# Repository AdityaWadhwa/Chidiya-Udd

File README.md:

# Chidiya-Udd
The title of the project “Chidiya udd” describes a popular Indian game which almost each Indian has played in their childhood. 

In the contemporary form, a person becomes a moderator and says the name of many objects which can either fly or they don’t and the players have to raise their finger in accordance with the object. 

This project replicates exactly the contemporary form but eliminating the need of a moderator which is fulfilled by the microcontroller. 
The project is developed under the guidance of Mr. D.V Gadre, CEDT lab in Netaji Subhas Institute of Technology (now, Netaji Subhas University of Technology). 

It was developed alongside my friend Sumiran Bhasin (https://github.com/sumiran14)

The microcontroller chosen is Texas Instruments low power device MSP430G2553.  

This project also interfaces two external SPI devices, the Graphics LCD and a flash memory; a speaker is used for the voice output.
The input from the player  is taken through a capacitive touch interface. 

As of now, it speaks only speaks in one language and only the name of the object. The next versions of the same project will have its own battery dependent power supply, better voice quality and more speed

The audio files are first downloaded (using Google translate) and converted and sampled at 8kHz and stored in 8 bit format(because human voice has maximum frequency of 4 kHZ and we sample it at at least twice that frequency) 
and saved in .wav format. Then using a software "WAVToCode" they are easily converted into c files. 
The data in the C files is really large so any microcontroller memory can’t fit all of that. 
So the data is sent through a python program from the PC to an Arduino and then written in external SPI Flash memory through Arduino.

When the data has to be played, MSP430 first fetches the data from SPI flash. 
That data decides the duty cycle of the PWM wave.The PWM wave is then sent as an input to a PAM IC and finally to a speaker to hear us the voice. As the data is sampled at 8Khz the duty cycle of the PWM wave has to be changed after every 1/8000th of a second i.e the next data is fetched from the external memory and played for 1/8000th of a second. 

The Graphics LCD is used to display the score. The code for the Graphics LCD is inspired by a blog by Rohit Gupta. 
Since timers are used for generating PWM, developing our own code for capacitive touch sensing was essential. 

In general, capacitive touch works on the basis of an oscillator with a capacitor. 
For a fixed period of time, the number of oscillations in that period would not vary much if the capacitance doesn’t change. 
Due to human interaction, capacitance of the circuit changes drastically and the variation in oscillations in the fixed time are different by a substantial amount causing us to detect a touch. 
MSP430G2553 have built in pin oscillators and by changing some values in registers we can make them enabled and use them as a clock source to one of the timers. 

The overall codeflow is that at the start the player has a fixed score of 9. The game doesn’t start as soon as the finger of the player isn’t on the touchplate and as one loses their score decreases. A random number generator generates a random number which calls a specific object. When the player has score 0 the reset button has to be pressed to play the game again.

Each code and EAGLE files for the same have been attached.

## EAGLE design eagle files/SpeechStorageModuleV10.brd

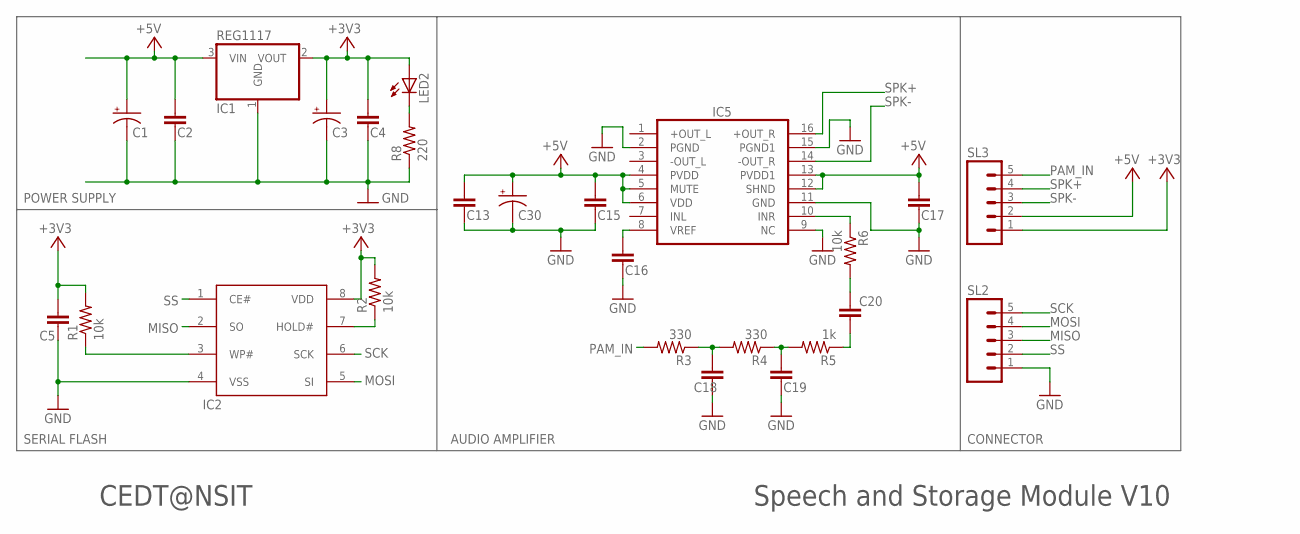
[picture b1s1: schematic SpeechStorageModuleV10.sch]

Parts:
C1, C3: 10u; C/6032-28R
C2, C4: 0.1uF; C1206
C5, C18: 0.1u; C0805
C13, C15, C17: 1uf; C1206
C16: 0.1uf; C1206
C19: 0.1uf; C0805
C20: 0.47uF; C0805
C30: 100u; C/6032-28R
IC1: REG1117; SOT223
IC2: SST25VF040B_SPI_FLASH; SOIC08
IC5: PAM8403; SOP-16
LED2: LED0805; CHIPLED_0805
R1, R2, R6: 10k; R0805
R3, R4: 330; R0805
R5: 1k; R0805
R8: 220; R0805
SL2, SL3: M05; 05P

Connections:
+3V3: C3.+, C4.2, C5.1, IC1.2 (VOUT), IC2.8 (VDD), LED2.A, R1.2, R2.2, SL3.1
+5V: C1.+, C2.2, C13.1, C15.2, C17.2, C30.+, IC1.3 (VIN), IC5.4 (PVDD), IC5.5 (MUTE), IC5.6 (VDD), IC5.12 (SHND), IC5.13 (PVDD1), SL3.2
GND: C1.-, C2.1, C3.-, C4.1, C5.2, C13.2, C15.1, C16.2, C17.1, C18.2, C19.2, C30.-, IC1.1 (GND), IC2.4 (VSS), IC5.2 (PGND), IC5.9 (NC), IC5.11 (GND), IC5.15 (PGND1), R8.1, SL2.1
MISO: IC2.2 (SO), SL2.3
MOSI: IC2.5 (SI), SL2.4
unnamed: IC2.7 (HOLD#), R2.1
unnamed: C18.1, R3.1, R4.2
unnamed: IC2.3 (WP#), R1.1
unnamed: C19.1, R4.1, R5.2
unnamed: C20.1, R5.1
unnamed: C20.2, R6.2
unnamed: LED2.C, R8.2
unnamed: IC5.10 (INR), R6.1
unnamed: C16.1, IC5.8 (VREF)
PAM_IN: R3.2, SL3.5
SCK: IC2.6 (SCK), SL2.5
SPK+: IC5.16 (+OUT_R), SL3.4
SPK-: IC5.14 (-OUT_R), SL3.3
SS: IC2.1 (CE#), SL2.2

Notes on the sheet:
POWER SUPPLY
SERIAL FLASH
CONNECTOR
AUDIO AMPLIFIER
Speech and Storage Module V10
CEDT@NSIT

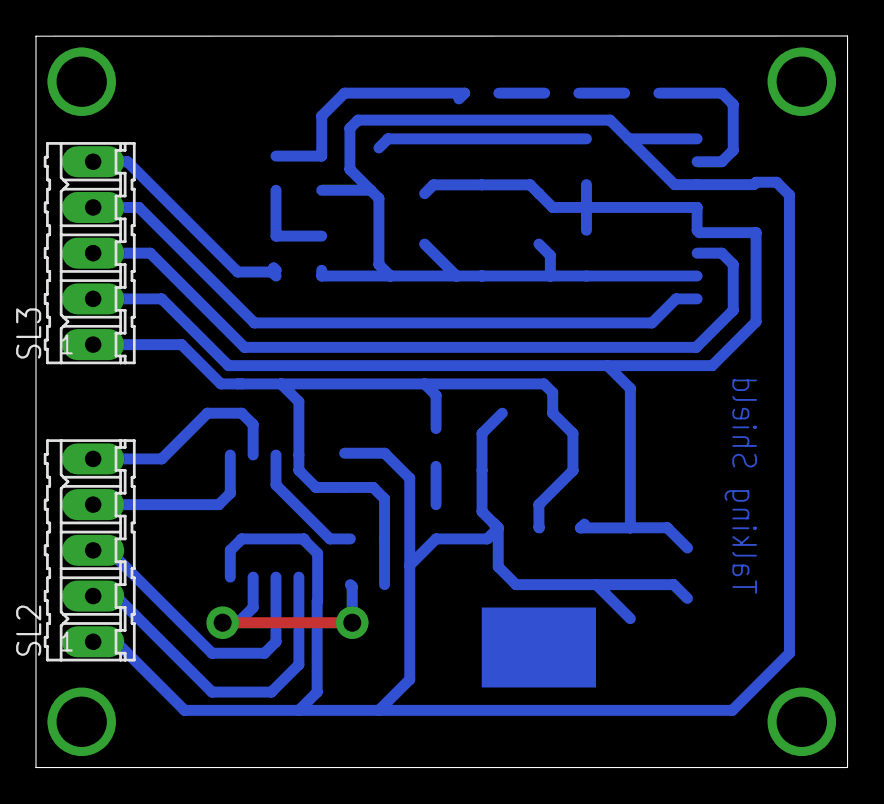
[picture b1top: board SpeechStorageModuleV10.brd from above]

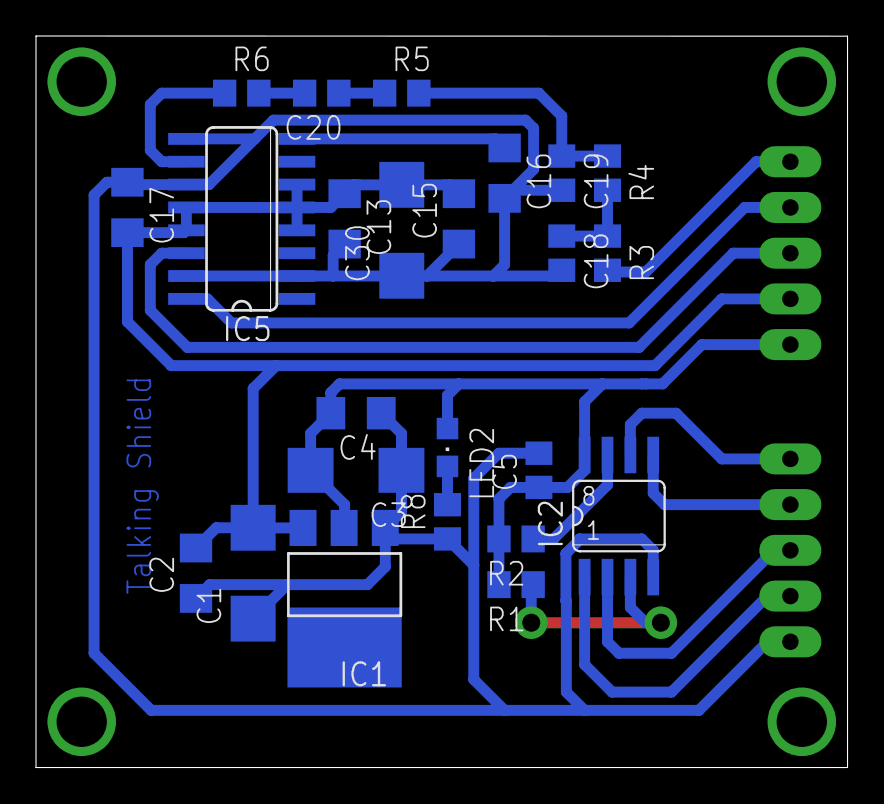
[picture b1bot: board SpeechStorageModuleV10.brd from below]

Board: 2 copper layers, 45.1 x 40.6 mm, 26 parts (24 on the bottom side), 19 nets.

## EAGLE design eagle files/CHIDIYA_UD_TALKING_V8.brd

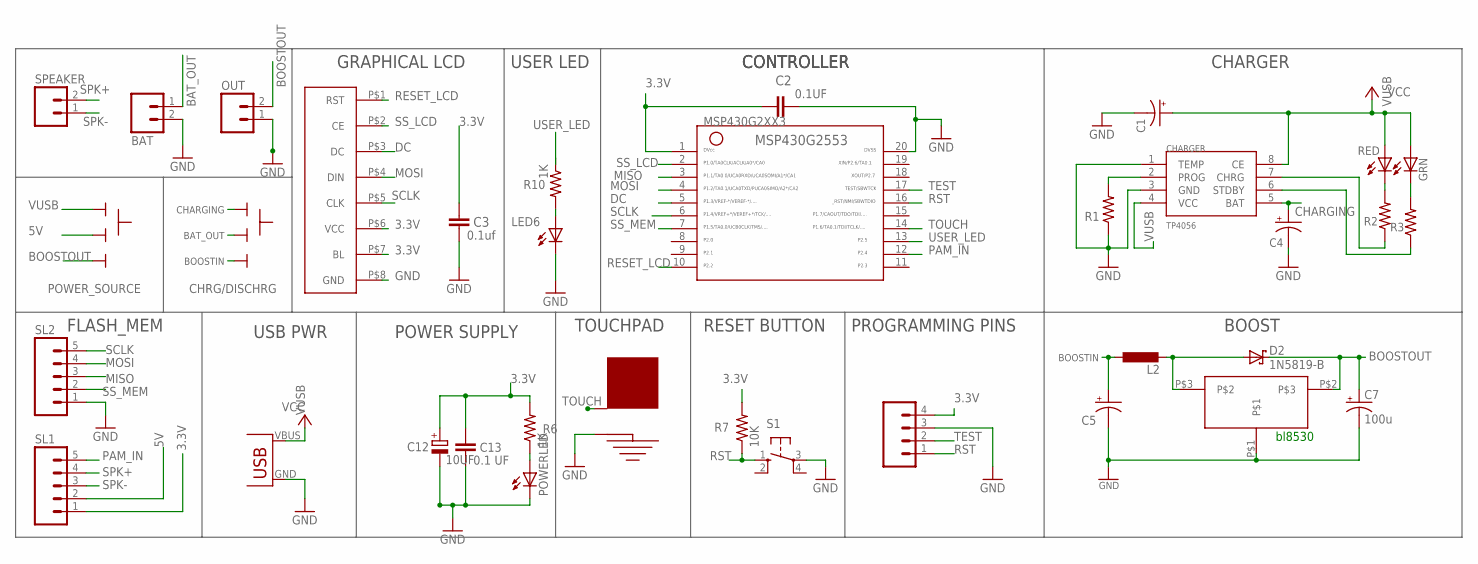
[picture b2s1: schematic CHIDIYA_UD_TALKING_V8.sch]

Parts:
BAT: M02; 02P
BOOST: BL8530_5V
C1, C4, C5: 10u; C/6032-28R
C2: 0.1UF; C050-025X075
C3: 0.1uf; C025-025X050
C7: 100u; C/6032-28R
C12: 10UF; E2,5-5
C13: 0.1 UF; C025-024X044
CHARGER: TP4056; SOP-8
CHRG/DISCHRG: SLIDESWITCH-BIG; BIGSWITCH
D2: 1N5819-B; DO41-7.6
GRN: LED3MM
L2: 47uH; L4532P
LED6: LED3MM
MSP430G2553: MSP430G2553DIP20; G2553-DIP20
OUT: M02; 02P
POWERLED: LED3MM
POWER_SOURCE: SLIDESWITCH-BIG; BIGSWITCH
PROGRAM: M04; 04P
R1: RESISTOR0805; R0805
R2, R3: 470; R0805
R6, R10: 1K; 0207/7
R7: 10K; 0207/7
RED: LED3MM
S1: 10-XX; B3F-10XX
SL1, SL2: M05; 05P
SPEAKER: M02; 02P
TOUCH1: TOUCHPAD-20MM
U$2: USB(POWER)
U$4: NOKIA_5110_LCD; NOKIA_5110_MODULE

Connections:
3.3V: C2.1, C3.1, C12.+, C13.1, MSP430G2553.1, PROGRAM.4, R6.2, R7.2, SL1.1, U$4.P$6 (VCC), U$4.P$7 (BL)
5V: POWER_SOURCE.2, SL1.2
BAT_OUT: BAT.1, CHRG/DISCHRG.2
BOOSTIN: C5.+, CHRG/DISCHRG.3, L2.1
BOOSTOUT: BOOST.P$2, C7.+, D2.C, OUT.2, POWER_SOURCE.3
CHARGING: C4.+, CHARGER.5 (BAT), CHRG/DISCHRG.1
DC: MSP430G2553.5, U$4.P$3 (DC)
GND: BAT.2, BOOST.P$1, C1.-, C2.2, C3.2, C4.-, C5.-, C7.-, C12.-, C13.2, CHARGER.1 (TEMP), CHARGER.3 (GND), LED6.K (C), MSP430G2553.20, OUT.1, POWERLED.K (C), PROGRAM.3, R1.1, S1.3, SL2.1, TOUCH1.GND, U$2.GND, U$4.P$8 (GND)
MISO: MSP430G2553.3, SL2.3
MOSI: MSP430G2553.4, SL2.4, U$4.P$4 (DIN)
unnamed: LED6.A, R10.2
unnamed: CHARGER.2 (PROG), R1.2
unnamed: CHARGER.7 (CHRG), R2.1
unnamed: CHARGER.6 (STDBY), R3.1
unnamed: R2.2, RED.K (C)
unnamed: BOOST.P$3, D2.A, L2.2
unnamed: POWERLED.A, R6.1
unnamed: GRN.K (C), R3.2
PAM_IN: MSP430G2553.12, SL1.5
RESET_LCD: MSP430G2553.10, U$4.P$1 (RST)
RST: MSP430G2553.16, PROGRAM.1, R7.1, S1.1 (S)
SCLK: MSP430G2553.6, SL2.5, U$4.P$5 (CLK)
SPK+: SL1.4, SPEAKER.2
SPK-: SL1.3, SPEAKER.1
SS_LCD: MSP430G2553.2, U$4.P$2 (CE)
SS_MEM: MSP430G2553.7, SL2.2
TEST: MSP430G2553.17, PROGRAM.2
TOUCH: MSP430G2553.14, TOUCH1.TOUCH
USER_LED: MSP430G2553.13, R10.1
VUSB: C1.+, CHARGER.4 (VCC), CHARGER.8 (CE), GRN.A, POWER_SOURCE.1, RED.A, U$2.VBUS (VCC)

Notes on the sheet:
GRAPHICAL LCD
USER LED
CONTROLLER
FLASH_MEM
POWER SUPPLY
TOUCHPAD
RESET BUTTON
PROGRAMMING PINS
bl8530
USB PWR
CHARGER
BOOST

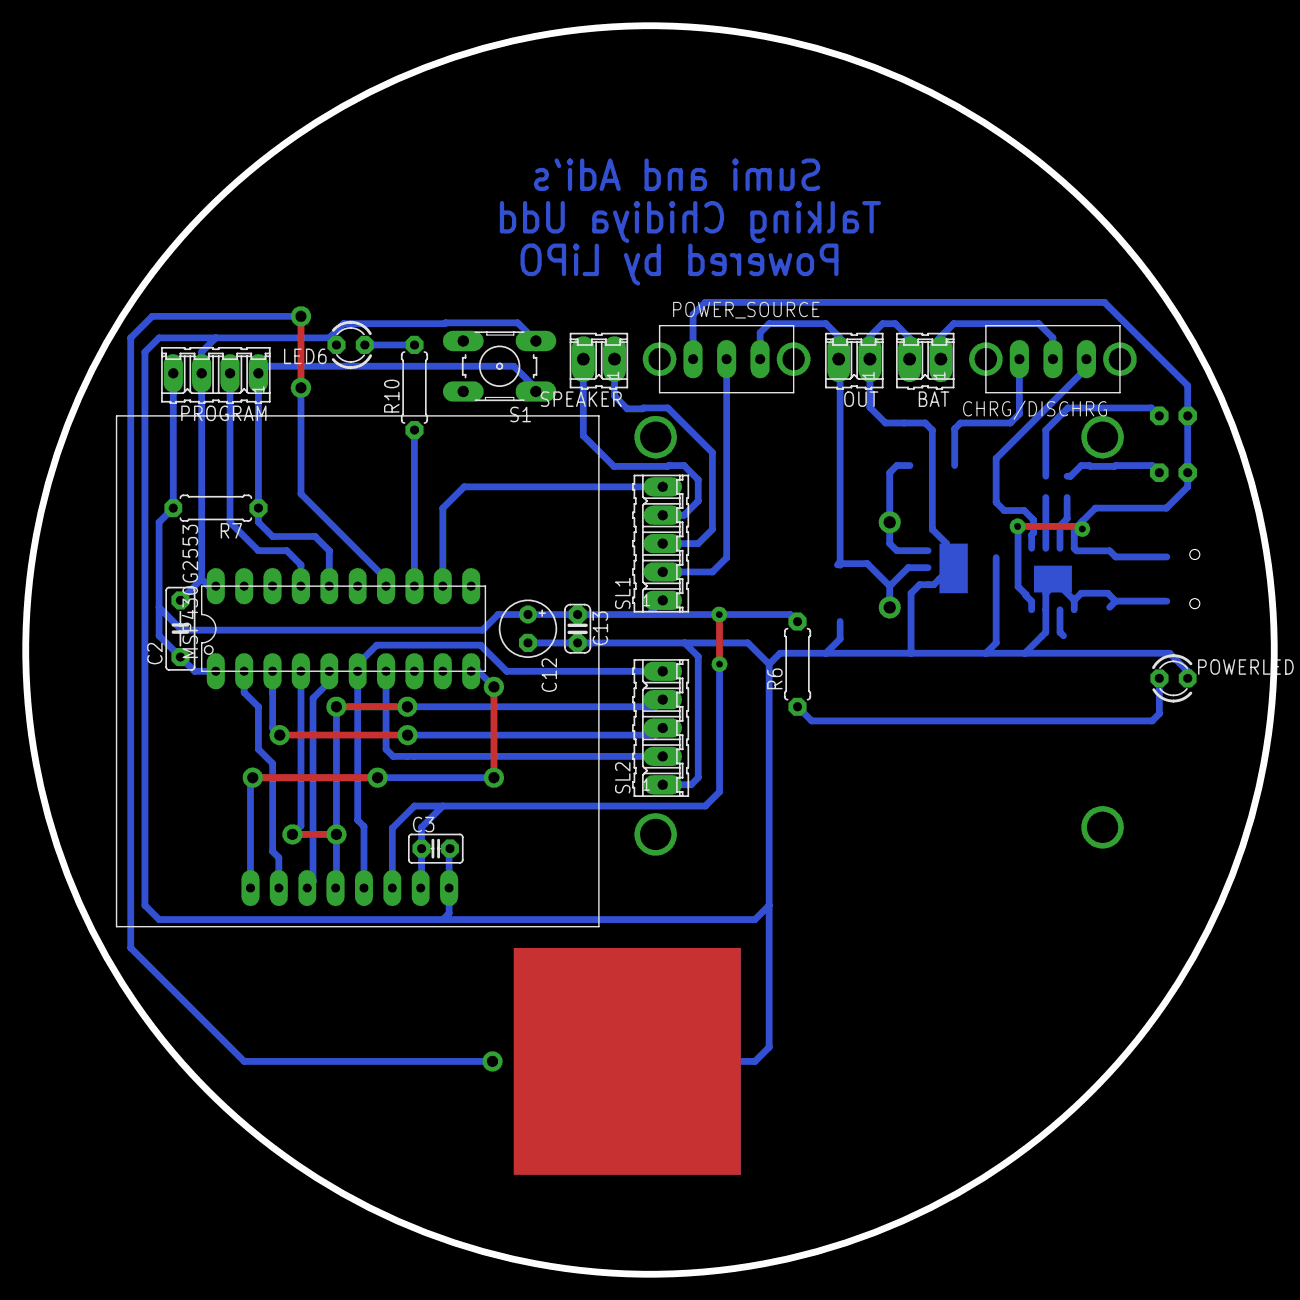
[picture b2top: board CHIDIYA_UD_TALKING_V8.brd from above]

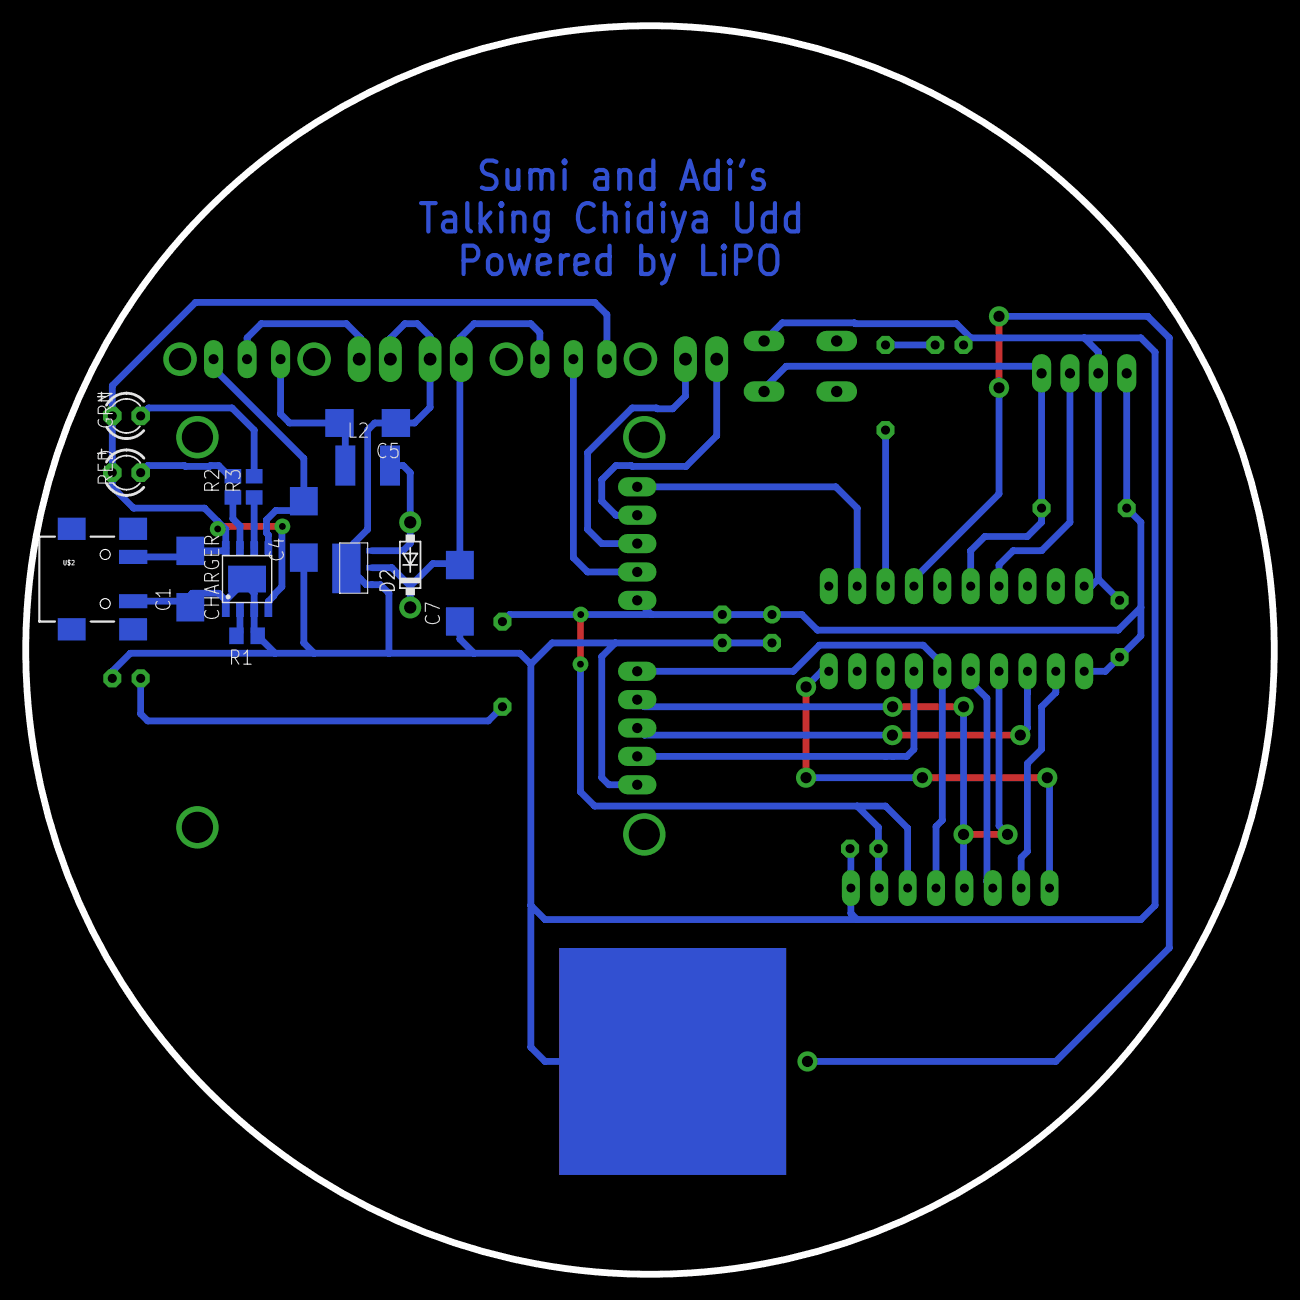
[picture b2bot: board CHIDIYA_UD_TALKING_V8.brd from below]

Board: 2 copper layers, 111.8 x 111.8 mm, 35 parts (14 on the bottom side), 30 nets.

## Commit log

2019-02-10 SPI flash writing through python
2019-02-10 Eagle files
2019-02-10 Arduino code
2019-02-10 MSP430 CCS Code

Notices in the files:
parts and their libraries:
SparkFun-Aesthetics: Licensing: Creative Commons ShareAlike 4.0 International - https://creativecommons.org/licenses/by-sa/4.0
